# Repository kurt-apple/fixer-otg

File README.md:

# fixer-otg
- Fork of [ChrisChrisLoLo/pusheenz40](https://github.com/ChrisChrisLoLo/pusheenz40). Also gathered info from [idawgz32](https://github.com/ChrisChrisLoLo/idawgz32) and [bunchiez40](https://github.com/ChrisChrisLoLo/bunchiez40).
- Layout is all-new, and design emphasizes ultra portable, small form factor while still having a fairly sane key map.
- Encased in epoxy for maximum durability and true pocketability
- Blog posts hosted on [Obsidian Publish](https://publish.obsidian.md/kurt/Maps/Fixer+OTG).
- **SHOWCASE MEDIA** is [here!](https://publish.obsidian.md/kurt/Pages/Fixer+OTG/Fixer+OTG+-+Showcase)
- FAK Firmware is [here!](https://github.com/kurt-apple/fak)

# Keyboard Design
As a parent, I often find myself "nap-trapped" but still needing to do computer work. After trying several Android touchscreen keyboards I have concluded that my fingers are not up for the task anymore. However, I still require a handheld form factor. More recently I spotted the uConsole from ClockworkPi and while it looks neat, I reason that if I have to wait many months to receive one, I might as well challenge myself to DIY. What could go wrong? 

The intent is to use these schematics (bunchiez40, pusheenz40, and idawgz32) as a launching-off point for an ambitious, DIY pocket keyboard, which will later evolve into a "deck" or "pocket" pc. Some requirements are currently listed in the [TODOs](TODO.md).

# Status
- prototype keyboard PCBs were ordered, arrived, I broke board 1 and board 2 is alive and well!
- Layout and firmware are made and I can achieve ~22 WPM on this layout!
- I've got my eyes set on a few display modules and I am interested in designing a CM4 carrier or picking another small SBC to dedicate to the cyberdeck project.

# Navigating the KiCad Files
I used a plugin called "Hierarchical-PCB" which allowed me to define a subcircuit for `switch_module` in separate `kicad_pcb` and `kicad_sch` files, then copy the layout specified in that `kicad_pcb` file whenever a hierarchical sheet of the same name is placed in the schematic of another PCB. The `switch_module` contains through-holes, diode positioning, and the necessary tracks for a single key.

> [!Warning]
> "Hierarchical-PCB" does not yet support nested hierarchical sheets. I forked the project and I want to try to add this support at a later date. Nevertheless, this plugin was VERY helpful in both making the schematic visually less noisy and also in quickly laying out tedious portions of the keyboard PCB.

To open the design I am using currently, please open the main `kicad_pcb` file titled `fixer-otg.kicad_pcb`.

# Making One
- DM me on Discord (@present_day) to check if I have any boards remaining
- Get yourself some Kailh Mute Micro Switches (42x)
- Fork my FAK repo for the firmware code, and modify however much you wish.
- Gather your soldering supplies
- My provided manufacturing files (gerber, drilling, BOM) are specifically for JLCPCB. If you want to print them at a different company you might have to output your own manufacturing files. Please note that there were a few minor corrections/alterations JLC made before finalizing their production file and proceeding to manufacturing. I am new at this - your experience may vary.
- All but the switches are placed/assembled by JLC.
- Receive your board(s)
- Recommended: flash firmware and short out each key by hand to make sure the keys work.
- Clone or fork the firmware repo and read code/make any customizations as you wish.
- `python fak.py compile -kb fixer-otg`
- plug in the board while holding the BOOT key (left of usb port)
- `python fak.py flash -kb fixer-otg`
- Solder the mute switches to each pad if you haven't done so already. Seal bottom of switches if you plan to epoxy (at your own risk!)
- Test it out

# Firmware Dependencies (Arch)
- python
- meson
- sdcc
- nickel

# BOM
This is the BOM. Note that most PCB prototype services have a minimum order quantity of around 5.
|  Comment | JLCPCB Part # | QTY | Price 5 Boards |
|---|---|---| --- |
| USB C Port | C165948 | 5 | $0.779 |
| CH552T | C111367 | 5 | $2.543 |
| 100nF Capacitor | C1525 | 10 | $0.012 |
| 5.1k Resistor | C25905 | 10 | $0.005 |
| 10k Resistor | C25744 | 5 | $0.003 |
| Diode | C2128 | 200 | $1.78 |

Some notes about my order and costs:
- PCB cost $19.60 in total for 5 boards.
- assembly cost $21.96 for 5 boards.
- shipping from JLC cost $22.80 to USA.
- the cost for switches varies widely; I bought from Kailh directly however Alibaba/Aliexpress have bulk lots of Kailh Micro switches for much cheaper.

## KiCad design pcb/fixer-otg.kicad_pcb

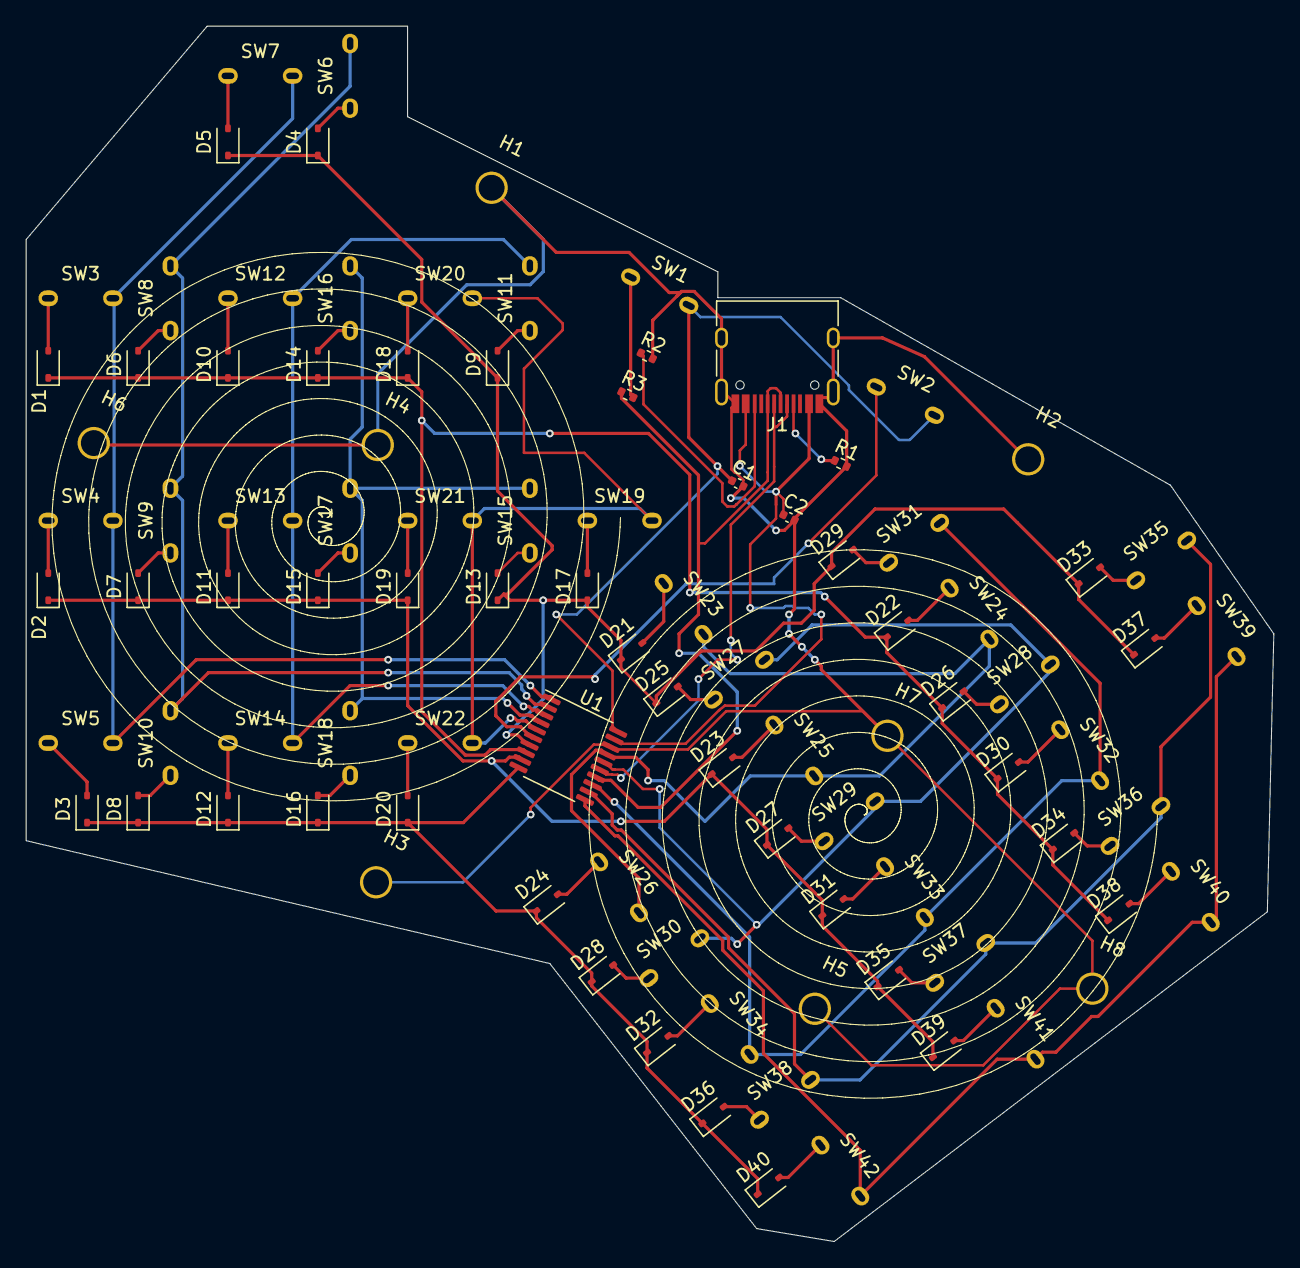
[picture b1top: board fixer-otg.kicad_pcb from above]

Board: 2 copper layers, 96.5 x 94.0 mm, 97 parts (0 on the bottom side), 63 nets.

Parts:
C1, C2: 100nF; C_0402_1005Metric
D1, D2, D3, D4, D5, D6, D7, D8, D9, D10, D11, D12, D13, D14, D15, D16, D17, D18, D19, D20, D21, D22, D23, D24, D25, D26, D27, D28, D29, D30, D31, D32, D33, D34, D35, D36, D37, D38, D39, D40: D_Small; D_SOD-323
H1, H2, H3, H4, H5, H6, H7, H8: MountingHole_Pad; m1.6_hole
J1: USB_C_Receptacle_USB2.0; USB_C_Receptacle_HRO_TYPE-C-31-M-12
R1, R2: 5.1k; R_0402_1005Metric
R3: 10k; R_0402_1005Metric
SW1: BOOT; Button_Mute_Kailh
SW2: RESET; Button_Mute_Kailh
SW3, SW4, SW5, SW6, SW7, SW8, SW9, SW10, SW11, SW12, SW13, SW14, SW15, SW16, SW17, SW18, SW19, SW20, SW21, SW22, SW23, SW24, SW25, SW26, SW27, SW28, SW29, SW30, SW31, SW32, SW33, SW34, SW35, SW36, SW37, SW38, SW39, SW40, SW41, SW42: SW_Push; Button_Mute_Kailh
U1: CH552T; TSSOP-20_4.4x6.5mm_P0.65mm

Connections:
+3.3V: C1.1, SW1.2, SW2.2, U1.20 (V33)
BOOT: R3.2, SW1.1
CC1: J1.A5 (CC1), R1.1
CC2: J1.B5 (CC2), R2.1
GND: C1.2, C2.2, H1.1, H2.1, H3.1, H4.1, H5.1, H6.1, H7.1, H8.1, J1.A1 (GND), J1.A12 (GND), J1.B1 (GND), J1.B12 (GND), J1.S1 (SHIELD), R1.2, R2.2, U1.18 (GND/VSS)
unnamed: D1.2 (A), SW3.1
unnamed: D2.2 (A), SW4.1
unnamed: D3.2 (A), SW5.1
unnamed: D4.2 (A), SW6.1
unnamed: D5.2 (A), SW7.1
unnamed: D6.2 (A), SW8.1
unnamed: D7.2 (A), SW9.1
unnamed: D8.2 (A), SW10.1
unnamed: D9.2 (A), SW11.1
unnamed: D10.2 (A), SW12.1
unnamed: D11.2 (A), SW13.1
unnamed: D12.2 (A), SW14.1
unnamed: D13.2 (A), SW15.1
unnamed: D14.2 (A), SW16.1
unnamed: D15.2 (A), SW17.1
unnamed: D16.2 (A), SW18.1
unnamed: D17.2 (A), SW19.1
unnamed: D18.2 (A), SW20.1
unnamed: D19.2 (A), SW21.1
unnamed: D20.2 (A), SW22.1
unnamed: D21.2 (A), SW23.1
unnamed: D22.2 (A), SW24.1
unnamed: D23.2 (A), SW25.1
unnamed: D24.2 (A), SW26.1
unnamed: D25.2 (A), SW27.1
unnamed: D26.2 (A), SW28.1
unnamed: D27.2 (A), SW29.1
unnamed: D28.2 (A), SW30.1
unnamed: D29.2 (A), SW31.1
unnamed: D30.2 (A), SW32.1
unnamed: D31.2 (A), SW33.1
unnamed: D32.2 (A), SW34.1
unnamed: D33.2 (A), SW35.1
unnamed: D34.2 (A), SW36.1
unnamed: D35.2 (A), SW37.1
unnamed: D36.2 (A), SW38.1
unnamed: D37.2 (A), SW39.1
unnamed: D38.2 (A), SW40.1
unnamed: D39.2 (A), SW41.1
unnamed: D40.2 (A), SW42.1
RST: SW2.1, U1.6 (RST/T2EX_/CAP2_)
UDM: J1.A7 (D-), J1.B7 (D-), U1.15 (P3.7/UDM)
UDP: J1.A6 (D+), J1.B6 (D+), R3.1, U1.14 (P3.6/UDP)
VBUS: C2.1, J1.A4 (VBUS), J1.A9 (VBUS), J1.B4 (VBUS), J1.B9 (VBUS), U1.19 (VCC/VDD)
col1: SW3.2, SW4.2, SW5.2, SW7.2, U1.1 (P3.2/TXD1_/INT0/VBUS1/AIN3)
col2: SW6.2, SW8.2, SW9.2, SW10.2, U1.2 (P1.4/T2_/CAP1_/SCS/TIN2/UCC1/AIN1)
col3: SW11.2, SW12.2, SW13.2, SW14.2, U1.3 (P1.5/MOSI/PWM1/TIN3/UCC2/AIN2)
col4: SW15.2, SW16.2, SW17.2, SW18.2, U1.4 (P1.6/MISO/RXD1/TIN4)
col5: SW19.2, SW20.2, SW21.2, SW22.2, U1.5 (P1.7/SCK/TXD1/TIN5)
col6: SW23.2, SW24.2, SW25.2, SW26.2, U1.17 (P1.2/XI/RXD_)
col7: SW27.2, SW28.2, SW29.2, SW30.2, U1.16 (P1.3/XO/TXD_)
col8: SW31.2, SW32.2, SW33.2, SW34.2, U1.13 (P3.5/T1)
col9: SW35.2, SW36.2, SW37.2, SW38.2, U1.12 (P3.4/PWM2/RXD1_/T0)
col10: SW39.2, SW40.2, SW41.2, SW42.2, U1.11 (P3.3/INT1)
row1: D4.1 (K), D5.1 (K), D9.1 (K), D13.1 (K), D17.1 (K), D21.1 (K), D25.1 (K), D29.1 (K), D33.1 (K), D37.1 (K), U1.7 (P1.0/T2/CAP1/TIN0)
row2: D1.1 (K), D6.1 (K), D10.1 (K), D14.1 (K), D18.1 (K), D22.1 (K), D26.1 (K), D30.1 (K), D34.1 (K), D38.1 (K), U1.8 (P1.1/T2EX/CAP2/TIN1/VBUS2/AIN0)
row3: D2.1 (K), D7.1 (K), D11.1 (K), D15.1 (K), D19.1 (K), D23.1 (K), D27.1 (K), D31.1 (K), D35.1 (K), D39.1 (K), U1.9 (P3.1/PWM2_/TXD)
row4: D3.1 (K), D8.1 (K), D12.1 (K), D16.1 (K), D20.1 (K), D24.1 (K), D28.1 (K), D32.1 (K), D36.1 (K), D40.1 (K), U1.10 (P3.0/PWM1_/RXD)

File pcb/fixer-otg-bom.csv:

Reference,Value,Datasheet,Footprint,Qty,DNP,JLCPCB Part#
"C1,C2",100nF,~,Library:C_0402_1005Metric,2,,C1525
"D1,D2,D3,D4,D5,D6,D7,D8,D9,D10,D11,D12,D13,D14,D15,D16,D17,D18,D19,D20,D21,D22,D23,D24,D25,D26,D27,D28,D29,D30,D31,D32,D33,D34,D35,D36,D37,D38,D39,D40",D_Small,~,Library:D_SOD-323,40,,C2128
J1,USB_C_Receptacle_USB2.0,https://www.usb.org/sites/default/files/documents/usb_type-c.zip,Library:USB_C_Receptacle_HRO_TYPE-C-31-M-12,1,,C165948
"R1,R2",5.1k,~,Library:R_0402_1005Metric,2,,C25905
R3,10k,~,Library:R_0402_1005Metric,1,,C25744
U1,CH552T,http://www.wch.cn/downloads/file/241.html,Library:TSSOP-20_4.4x6.5mm_P0.65mm,1,,C111367

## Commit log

2024-08-23 fixer otg kicad
2024-08-23 manufacturing directory
2024-08-23 added link to firmware repo
2024-08-23 refinement of readme
2024-08-23 BOM table
2024-08-23 clarification and formatting
2024-08-23 Dollar Signs
2024-08-24 dependencies list
2024-08-24 deps
2025-03-11 Create kmk_code
2025-03-11 Rename kmk_code to kmk_code.py
2025-03-16 v2 config rev A
2025-03-19 latest firmware config for v2 fixer board...
2025-03-19 layout much better now... still unsure about a few keys
2025-09-30 Latest kmk_code.py for fixer-v2
